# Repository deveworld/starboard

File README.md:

# Starboard

Starboard is a compact Hackpad macropad using only kit parts: six MX-style switches, one EC11 encoder, one 0.91 inch OLED, six SK6812 MINI-E LEDs, and a Seeed XIAO RP2040.

**Live demo → <https://deveworld.github.io/starboard/>** — interactive 3D viewer, specs, and downloads.

The current case model is `CAD/assembled-model.STEP`, which includes the case and assembled components.

## Renders / Screenshots

| Schematic | PCB front | PCB back |
| :---: | :---: | :---: |
|  |  |  |

## Bill of Materials

| Part | Qty |
| --- | ---: |
| Seeed XIAO RP2040 | 1 |
| MX-style mechanical switch | 6 |
| Blank DSA keycap | 6 |
| EC11 rotary encoder, 20mm D-shaft | 1 |
| 0.91 inch 128x32 OLED display | 1 |
| SK6812 MINI-E RGB LED | 6 |
| 1N4148 through-hole diode | 6 |
| M3x16mm screw | 4 |
| M3x5x4mm heatset insert | 4 |

## Design Summary

- PCB size: 63.0 x 63.0 mm, 2 layers
- Case size: 83.8 x 83.8 x 18.5 mm
- Inputs: 6 switches + 1 encoder
- MCU: Seeed XIAO RP2040
- Case: fully 3D printed sandwich case, top plate + bottom shell
- Switch plate: 1.5 mm thick, 14.2 x 14.2 mm MX cutouts
- Top shell: integrated 3.0 mm reinforced perimeter with screw head counterbores
- Fasteners: M3x16 screws into M3x5x4 heatset inserts

## Firmware

- QMK source: `Firmware/qmk/starboard/`
- Production archive: `production/firmware-qmk.zip`
- Prebuilt UF2: `production/firmware.uf2`
- Build command: `qmk compile -kb starboard -km default`
- Features: 6-key matrix, encoder rotation, encoder press, SSD1306 OLED, SK6812 RGB lighting
- Configurator: **<https://deveworld.github.io/starboard/configure/>** remaps keys and the encoder, sets lighting, writes custom OLED text and records macros over WebHID (Chrome/Edge). The firmware speaks the VIA protocol, with OLED settings on VIA's custom channel.
- Flashing an assembled board: hold FN (bottom-right key) and press the top-left key to enter the bootloader, then copy the UF2 onto the `RPI-RP2` drive.
- Wireless note: the current XIAO RP2040 hardware has no BLE radio; ZMK wireless should be reserved for a future BLE-controller revision.

## Submission Files

- `CAD/assembled-model.STEP`
- `Firmware/qmk/starboard/`
- `PCB/starboard.kicad_pro`
- `PCB/starboard.kicad_sch`
- `PCB/starboard.kicad_pcb`
- `production/firmware-qmk.zip`
- `production/gerbers.zip`
- `production/firmware.uf2`
- `production/Top.STEP`
- `production/Bottom.STEP`

## Verification

- ERC: 0 errors, 6 symbol-library mismatch warnings for SK6812 cache copies.
- DRC: 0 errors, 0 unconnected pads, 0 schematic parity issues; remaining warnings are silkscreen/cosmetic.
- Case V5 fit audit: all boolean clash and clearance checks pass.
- Firmware package: `keyboard.json` parses successfully, `production/firmware-qmk.zip` passes zip integrity check, and QMK compile succeeds for `starboard:default`.

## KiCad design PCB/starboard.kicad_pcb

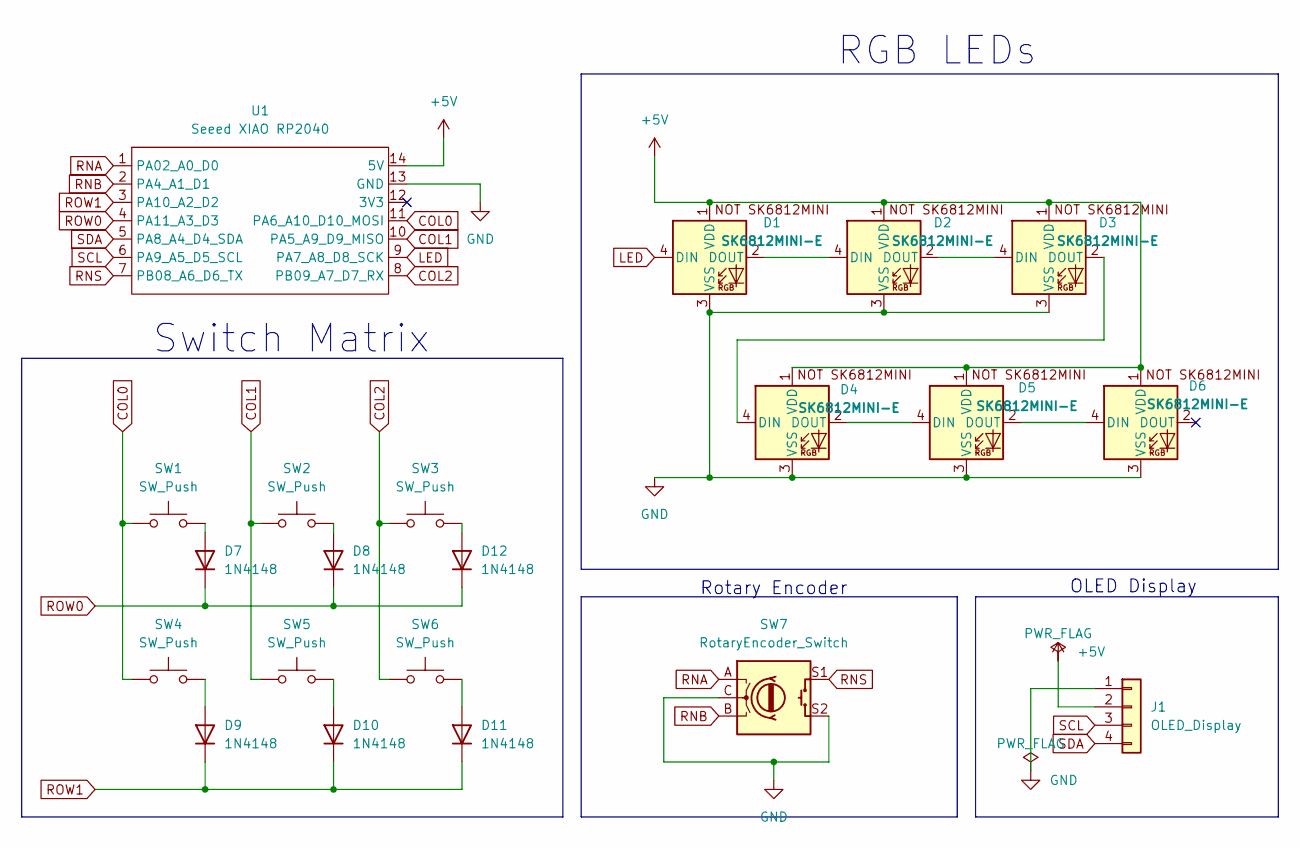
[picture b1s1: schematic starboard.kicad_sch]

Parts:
D1, D2, D3, D4, D5, D6: SK6812MINI-E; SK6812MINI-E_fixed
D7, D8, D9, D10, D11, D12: 1N4148; D_DO-35_SOD27_P7.62mm_Horizontal
J1: OLED_Display; SSD1306-0.91-OLED-4pin-128x32
SW1, SW2, SW3, SW4, SW5, SW6: SW_Push; SW_Cherry_MX_1.00u_PCB
SW7: RotaryEncoder_Switch; RotaryEncoder_Alps_EC11E-Switch_Vertical_H20mm
U1: Seeed XIAO RP2040; XIAO-Generic-Hybrid-14P-2.54-21X17.8MM

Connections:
+5V: D1.1 (VDD), D2.1 (VDD), D3.1 (VDD), D4.1 (VDD), D5.1 (VDD), D6.1 (VDD), J1.2, U1.14 (5V)
COL0: SW1.1, SW4.1, U1.11 (PA6_A10_D10_MOSI)
COL1: SW2.1, SW5.1, U1.10 (PA5_A9_D9_MISO)
COL2: SW3.1, SW6.1, U1.8 (PB09_A7_D7_RX)
GND: D1.3 (VSS), D2.3 (VSS), D3.3 (VSS), D4.3 (VSS), D5.3 (VSS), D6.3 (VSS), J1.1, SW7.C, SW7.S2, U1.13 (GND)
LED: D1.4 (DIN), U1.9 (PA7_A8_D8_SCK)
unnamed: D1.2 (DOUT), D2.4 (DIN)
unnamed: D2.2 (DOUT), D3.4 (DIN)
unnamed: D3.2 (DOUT), D4.4 (DIN)
unnamed: D4.2 (DOUT), D5.4 (DIN)
unnamed: D5.2 (DOUT), D6.4 (DIN)
unnamed: D7.2 (A), SW1.2
unnamed: D8.2 (A), SW2.2
unnamed: D9.2 (A), SW4.2
unnamed: D10.2 (A), SW5.2
unnamed: D11.2 (A), SW6.2
unnamed: D12.2 (A), SW3.2
RNA: SW7.A, U1.1 (PA02_A0_D0)
RNB: SW7.B, U1.2 (PA4_A1_D1)
RNS: SW7.S1, U1.7 (PB08_A6_D6_TX)
ROW0: D7.1 (K), D8.1 (K), D12.1 (K), U1.4 (PA11_A3_D3)
ROW1: D9.1 (K), D10.1 (K), D11.1 (K), U1.3 (PA10_A2_D2)
SCL: J1.3, U1.6 (PA9_A5_D5_SCL)
SDA: J1.4, U1.5 (PA8_A4_D4_SDA)

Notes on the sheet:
RGB LEDs
Rotary Encoder
OLED Display
Switch Matrix

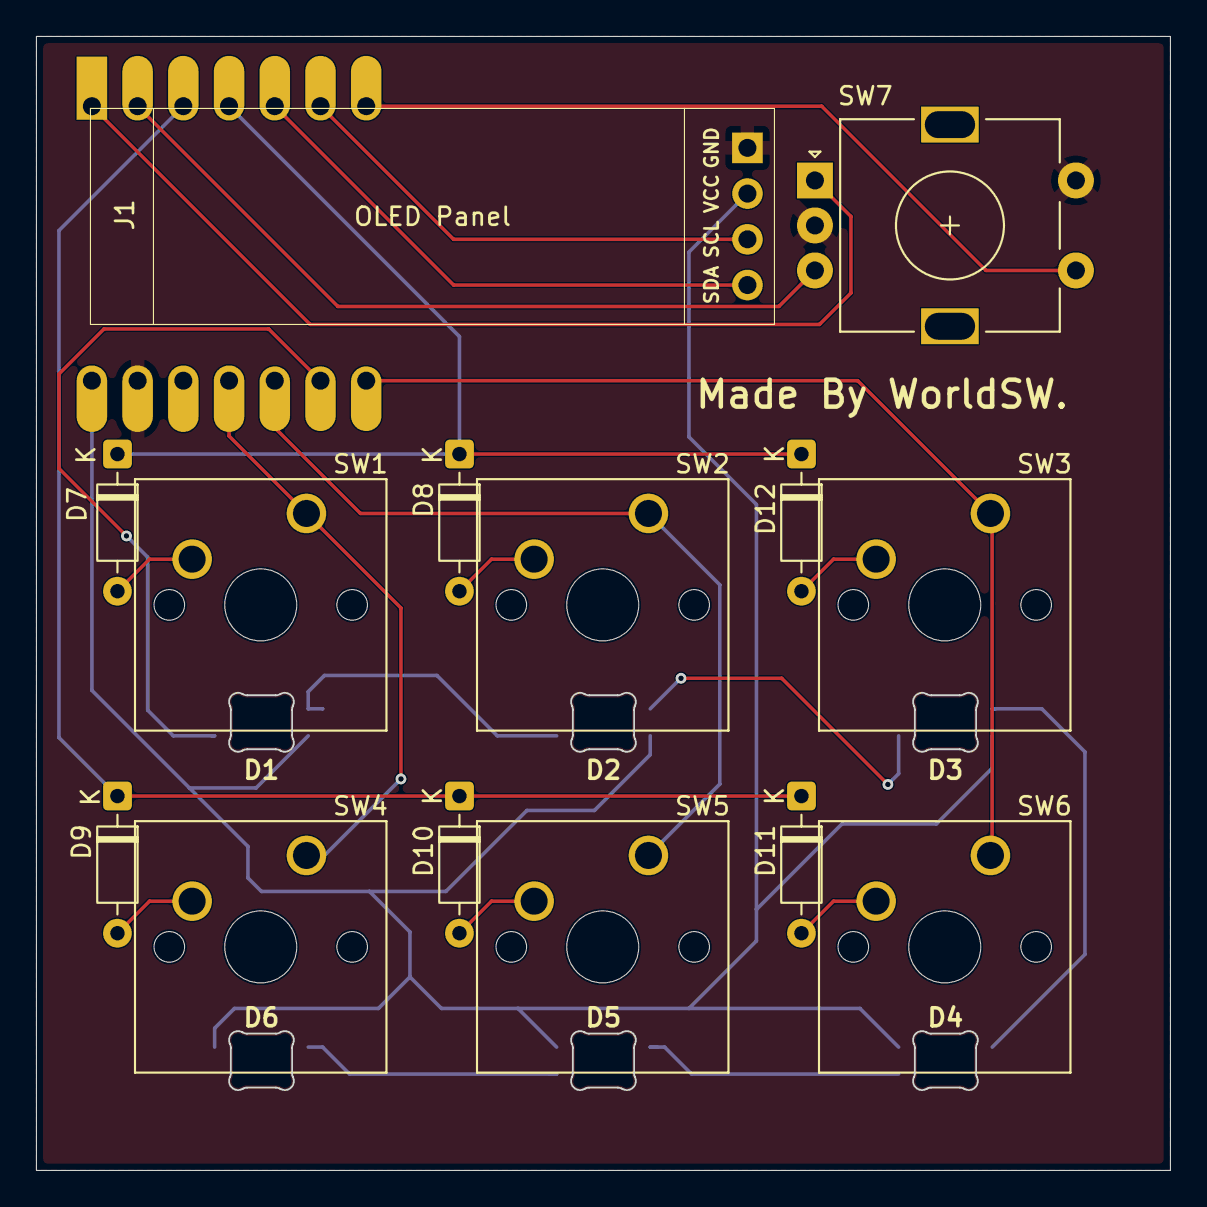
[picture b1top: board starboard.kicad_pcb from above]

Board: 2 copper layers, 62.9 x 63.0 mm, 21 parts (1 on the bottom side), 24 nets.

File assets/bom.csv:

"Refs","Value","Footprint","Qty","DNP"
"D1","SK6812MINI-E","footprints:SK6812MINI-E_fixed","1",""
"D2","SK6812MINI-E","footprints:SK6812MINI-E_fixed","1",""
"D3","SK6812MINI-E","footprints:SK6812MINI-E_fixed","1",""
"D4","SK6812MINI-E","footprints:SK6812MINI-E_fixed","1",""
"D5","SK6812MINI-E","footprints:SK6812MINI-E_fixed","1",""
"D6","SK6812MINI-E","footprints:SK6812MINI-E_fixed","1",""
"D7","1N4148","Diode_THT:D_DO-35_SOD27_P7.62mm_Horizontal","1",""
"D8","1N4148","Diode_THT:D_DO-35_SOD27_P7.62mm_Horizontal","1",""
"D9","1N4148","Diode_THT:D_DO-35_SOD27_P7.62mm_Horizontal","1",""
"D10","1N4148","Diode_THT:D_DO-35_SOD27_P7.62mm_Horizontal","1",""
"D11","1N4148","Diode_THT:D_DO-35_SOD27_P7.62mm_Horizontal","1",""
"D12","1N4148","Diode_THT:D_DO-35_SOD27_P7.62mm_Horizontal","1",""
"J1","OLED_Display","footprints:SSD1306-0.91-OLED-4pin-128x32","1",""
"SW1","SW_Push","Button_Switch_Keyboard:SW_Cherry_MX_1.00u_PCB","1",""
"SW2","SW_Push","Button_Switch_Keyboard:SW_Cherry_MX_1.00u_PCB","1",""
"SW3","SW_Push","Button_Switch_Keyboard:SW_Cherry_MX_1.00u_PCB","1",""
"SW4","SW_Push","Button_Switch_Keyboard:SW_Cherry_MX_1.00u_PCB","1",""
"SW5","SW_Push","Button_Switch_Keyboard:SW_Cherry_MX_1.00u_PCB","1",""
"SW6","SW_Push","Button_Switch_Keyboard:SW_Cherry_MX_1.00u_PCB","1",""
"SW7","RotaryEncoder_Switch","footprints:RotaryEncoder_Alps_EC11E-Switch_Vertical_H20mm","1",""
"U1","Seeed XIAO RP2040","footprints:XIAO-Generic-Hybrid-14P-2.54-21X17.8MM","1",""

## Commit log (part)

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2026-06-13 Starboard macropad submission
    XIAO RP2040 6-key + EC11 encoder macropad (Hackpad, kit parts).
    - PCB 63x63mm 2-layer (KiCad), gerbers + drill in production/
    - QMK firmware (Firmware/qmk/starboard) + compiled production/firmware.uf2
    - 3D-printed sandwich case (Top/Bottom STEP, assembled model)
    - BOM + schematic/PCB/case renders in README
2026-06-13 README: lead with assembled case render, move other images into a compact table
2026-06-13 README: constrain hero render to 500px, centered
2026-06-13 Add static Next.js demo site (web/)
    Single-page showcase: hero render, features, specs, default keymap,
    KiCad design-file gallery, BOM, and download links. Next.js 15 App
    Router + Tailwind v4, static export to web/out/ (npm run build).
2026-06-13 Redesign demo site: editorial/technical aesthetic
    Drop the generic dark-neon look (gradients, glow, emoji icons, rounded
    glass cards) for a Swiss/datasheet style: paper + ink palette, monospace
    labels, hairline grid, numbered ruled rows, figure captions.
2026-06-13 Interactive 3D viewer + design-file lightbox
    - Replace the static hero render with a three.js GLTF viewer (orbit,
    zoom, auto-rotate); STEP converted to a 3 MB colored .glb. PNG stays
    as a poster/WebGL fallback.
    - Design-file figures open in a fullscreen lightbox on click (Esc or
    click to close).
2026-06-13 Fix blank 3D viewer: scale OrbitControls distance to model
    The GLB exports in metres (~0.084 max dim) but min/maxDistance were mm-scale
    (30/400), so OrbitControls clamped the camera ~30 m away and the model
    rendered as an invisible dot. Derive distance limits from the model size.
    Also set metadataBase and suppressHydrationWarning (browser extensions
    mutate <html> and trip React hydration).
2026-06-13 Deploy to GitHub Pages via Actions
    - basePath/assetPrefix from NEXT_PUBLIC_BASE_PATH (=/starboard in CI),
    with an asset() helper to prefix raw <img>/GLTF/fetch URLs.
    - GitHub Actions workflow: build static export and publish to Pages.
    - .nojekyll so the _next directory is served.
2026-06-13 README: add live demo link
